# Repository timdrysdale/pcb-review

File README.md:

# pcb-review
Documents to help with reviewing printed circuit board designs for remote laboratory experiments

## Background

PCB design is often about keeping track of the impacts of lots of small tid bits of data. Small mistakes can range from the merely annoying to the moderately expensive. Some of the things that can go wrong with even relatively simple embedded systems include putting a footprint down that is the wrong size, or the wrong way up, getting the polarity of a connector backwards,  getting pin headers that only take a round pin when your daughteroard is supplied with square pins, oversizing a track because you remembered the stall current from a motor wrong, forgetting to put pull-ups on an I2C bus, then adding them when they are not needed on a level shifting circuit which has it's own pullups, not leaving space around a terminal block to get wires in, leaving off mounting holes for the PCB, selecting the wrong pins on a microcontroller because you thought you'd use `analogWrite` then you device you want a different pulse width modulation frequency, so you need to use `SAMD21_Turbo_PWM`, needing to add a level shifter, needing to change the pin you get your 5V reference from when you change the arduino type from nano to nano every. Some of these have happened to us, and some of them nearly happened. Since there is an awful lot to keep a track of, I thought I'd try and formulate a design document that works for us (skip some of things we don't need to worry about, and add in some things that we do).

Ideally we'd also have a change control process so that we only have to sign off again on bits that have changed ...

A spreadsheet is probably a useful way to address this issue.

## Usage of this repo

I'm assuming that the templates might be better kept up to date if the actual reviews are stored in the same repo - they can also be copied into the project repos, or done in the project repo and then copied in here - that way, boards with similar parts can find checks in pre-existing design reviews to draw on.

Suggested review folder structure:
`review.ods`: the review spreadsheet
`design.md`: any design descriptions, and useful notes e.g. checking orientation and sizing of parts. 
`doc`: datasheets and application notes
`pcb`: the actual design files under review (complete, including all footprints)

```
├── example
│   ├── doc
│   └── pcb
└── pidcontrol2
    ├── doc
    └── pcb
```

## Developer notes

A guide to conditional formatting in LibreOffice Calc is [here](https://wiki.documentfoundation.org/images/d/d1/LibreOffice_Calc._Conditional_formatting_guide_EN.pdf)

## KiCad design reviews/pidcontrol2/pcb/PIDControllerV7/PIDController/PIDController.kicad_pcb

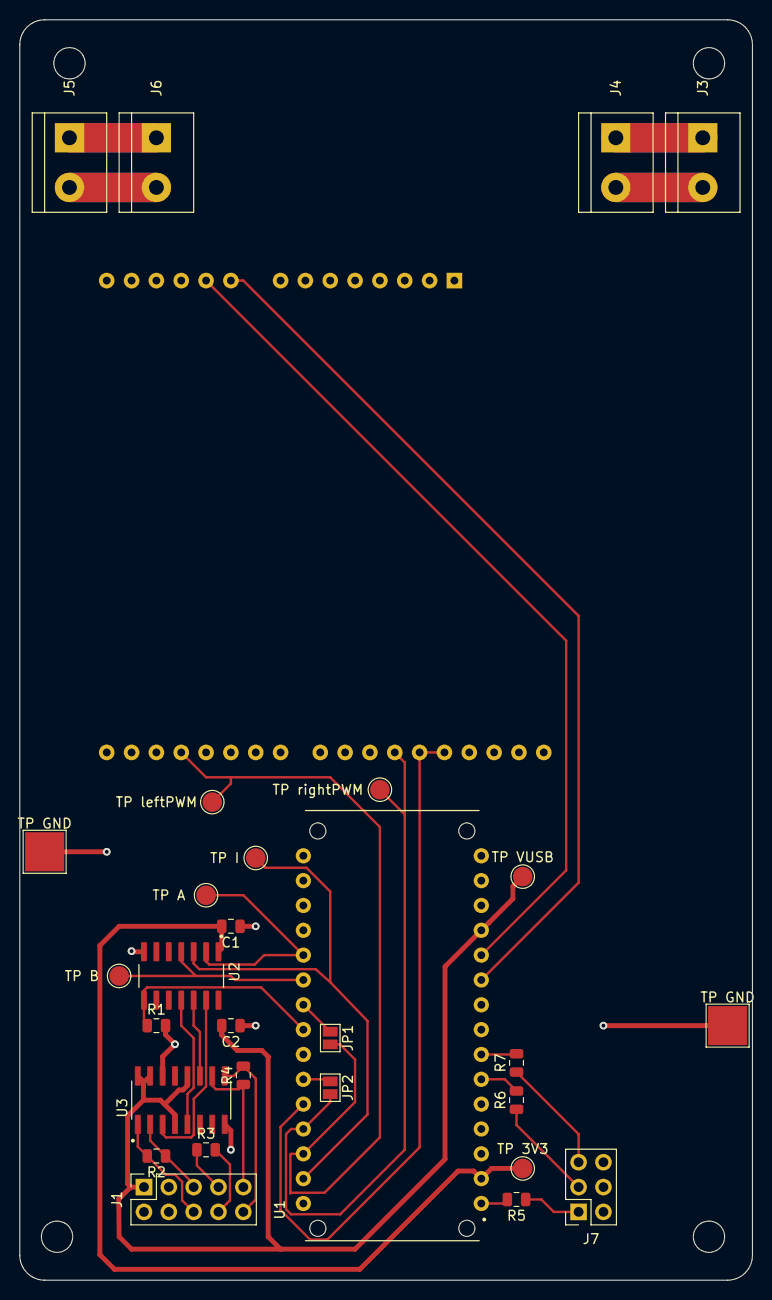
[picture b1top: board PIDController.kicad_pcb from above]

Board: 2 copper layers, 74.9 x 128.9 mm, 30 parts (1 on the bottom side), 34 nets.

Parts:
A1: Arduino_UNO_R3
C1, C2: 0.1uF; C_0805_2012Metric
J1: Conn_02x05_Odd_Even; PinSocket_2x05_P2.54mm_Vertical
J3, J4, J5, J6: Screw_Terminal_01x02; TerminalBlock_bornier-2_P5.08mm
J7: Conn_02x03_Odd_Even; PinSocket_2x03_P2.54mm_Vertical
JP1, JP2: SolderJumper_2_Open; SolderJumper-2_P1.3mm_Open_Pad1.0x1.5mm
R1: 5k; R_0805_2012Metric
R2, R3, R4: 2k; R_0805_2012Metric
R5, R6, R7: 200; R_0805_2012Metric
TP 3V3: TestPoint; TestPoint_Pad_D2.0mm
TP A: TestPoint; TestPoint_Pad_D2.0mm
TP B: TestPoint; TestPoint_Pad_D2.0mm
TP GND: TestPoint; TestPoint_Pad_4.0x4.0mm
TP GND#2: TestPoint; TestPoint_Pad_4.0x4.0mm
TP I: TestPoint; TestPoint_Pad_D2.0mm
TP VUSB: TestPoint; TestPoint_Pad_D2.0mm
TP leftPWM: TestPoint; TestPoint_Pad_D2.0mm
TP rightPWM: TestPoint; TestPoint_Pad_D2.0mm
U1: Arduino_Nano_33_IoT; MODULE_ABX00027
U2: TXS0104ED; SOIC127P600X175-14N
U3: SN75175D; SOIC127P600X175-16N

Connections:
3V3: C1.2, TP 3V3.1, U1.2, U2.1
A: U2.13, U3.3
B: U2.11, U3.5
CURRENT_1: A1.9, U1.10
CURRENT_2: A1.10, U1.11
ENABLE: A1.27, A1.28, U1.26
ENCODER_A: J1.5, R2.1, U3.2
ENCODER_B: J1.7, R3.1, U3.6
ENCODER_INDEX: J1.9, R4.1, U3.10
ENCODER_NOT_A: J1.6, R2.2, U3.1
ENCODER_NOT_B: J1.8, R3.2, U3.7
ENCODER_NOT_INDEX: J1.10, R4.2, U3.9
GND: A1.6, A1.7, A1.29, C1.1, C2.1, J1.4, J7.2, J7.4, J7.6, R1.2, TP GND.1, TP GND#2.1, U1.14, U1.19, U2.7, U3.8, U3.14
I: U2.12, U3.11
LED1: R5.2, U1.1
LED2: R6.2, U1.6
LED3: R7.2, U1.7
unnamed: J3.1, J4.1
unnamed: J3.2, J4.2
unnamed: J5.1, J6.1
unnamed: J5.2, J6.2
unnamed: J7.1, R5.1
unnamed: J7.3, R6.1
unnamed: J7.5, R7.1
unnamed: JP1.1, U1.22
unnamed: JP2.1, U1.25
unnamed: U1.13, U1.18
OE: R1.1, U1.23, U2.8
PIN_A: TP A.1, U1.20, U2.2
PIN_B: TP B.1, U1.21, U2.4
PIN_INDEX: TP I.1, U1.29, U2.3
VUSB: C2.2, J1.1, TP VUSB.1, U1.12, U2.14, U3.4, U3.12, U3.15, U3.16
leftPWM: A1.18, JP1.2, TP leftPWM.1, U1.28
rightPWM: A1.26, JP2.2, TP rightPWM.1, U1.27

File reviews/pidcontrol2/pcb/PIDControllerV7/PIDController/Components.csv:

Comment,Designator,Footprint
200 C17540,"R6,R7,R5",R_0805_2012Metric
,A1,Arduino_UNO_R3
SN75175D,U3,SOIC127P600X175-16N
0.1uF C49678,"C1,C2",C_0805_2012Metric
C8465 ,"J3,J4,J5,J6",TerminalBlock_bornier-2_P5.08mm
5k C78980,R1,R_0805_2012Metric
2k C17604,"R2,R3,R4",R_0805_2012Metric
,U1,MODULE_ABX00027
TXS0104ED,U2,SOIC127P600X175-14N
C5665 ,J1,PinSocket_2x05_P2.54mm_Vertical
C11214 ,J7,PinSocket_2x03_P2.54mm_Vertical
,"JP1,JP2",SolderJumper-2_P1.3mm_Open_Pad1.0x1.5mm
,"TP A,TP B,TP I,TP leftPWM,TP rightPWM,TP VUSB,TP 3V3",TestPoint_Pad_D2.0mm
,"TP GND,TP GND",TestPoint_Pad_4.0x4.0mm

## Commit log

2021-11-12 Add first attempt at template
2021-11-12 Update directory structure for templates
2021-11-12 Separate template into top level dir
2021-11-12 Add review doc to pidcontrol2
2021-11-12 Added checks on Nano
2021-11-12 Move review to main folder of picontrol2
2021-11-12 Added checks on motor shield to pidcontrol2
2021-11-19 Update template and PIDControl review
2021-11-22 update to PIDControllerv8 and updated review of pidcontrol2.
